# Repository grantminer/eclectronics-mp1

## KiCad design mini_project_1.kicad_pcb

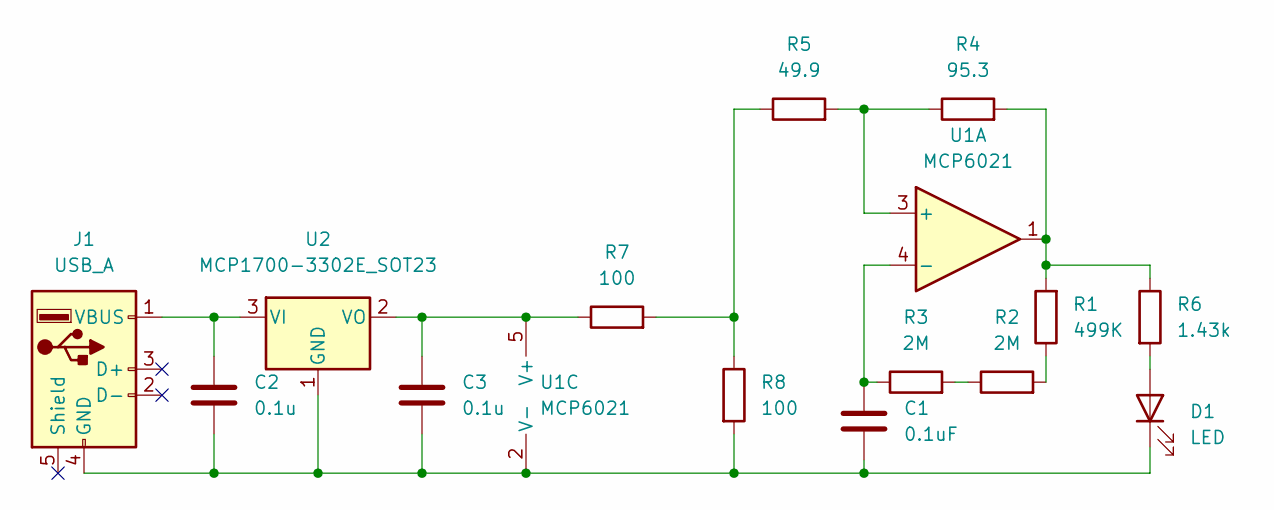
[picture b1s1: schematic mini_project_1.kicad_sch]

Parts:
C1: 0.1uF; C_0603_1608Metric
C2, C3: 0.1u; C_0603_1608Metric
D1: LED; D_0805_2012Metric
J1: USB_A; MOLEX_48037-0001
R1: 499K; R_0603_1608Metric
R2, R3: 2M; R_0603_1608Metric
R4: 95.3; R_0603_1608Metric
R5: 49.9; R_0603_1608Metric
R6: 1.43k; R_0603_1608Metric
R7, R8: 100; R_0603_1608Metric
U1: MCP6021; SOT-23-5
U2: MCP1700-3302E_SOT23; SOT-23

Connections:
unnamed: C1.1, R3.1, U1.4 (-)
unnamed: C1.2, C2.2, C3.2, D1.1 (K), J1.4 (GND), R8.2, U1.2 (V-), U2.1 (GND)
unnamed: C2.1, J1.1 (VBUS), U2.3 (VI)
unnamed: C3.1, R7.1, U1.5 (V+), U2.2 (VO)
unnamed: D1.2 (A), R6.2
unnamed: R1.1, R2.2
unnamed: R1.2, R4.2, R6.1, U1.1
unnamed: R2.1, R3.2
unnamed: R4.1, R5.2, U1.3 (+)
unnamed: R5.1, R7.2, R8.1

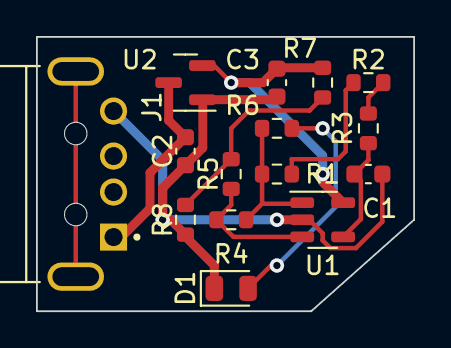
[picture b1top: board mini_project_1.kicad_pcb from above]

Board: 2 copper layers, 21.0 x 15.2 mm, 15 parts (0 on the bottom side), 10 nets.

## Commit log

2022-09-16 Resistor value tuning and worst case analysis
2022-09-16 Kicad design files and downloaded usb footprint
2022-09-16 Auto-generated Bill of Materials from Kicad
